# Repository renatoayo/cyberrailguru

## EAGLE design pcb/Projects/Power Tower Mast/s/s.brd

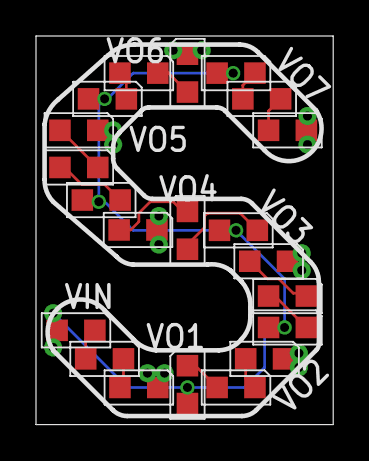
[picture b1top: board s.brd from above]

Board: 2 copper layers, 16.5 x 21.6 mm, 37 parts (0 on the bottom side), 22 nets.

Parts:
LED1, LED2, LED3, LED4, LED5, LED6, LED7, LED8, LED9, LED10, LED11, LED12, LED13, LED14, LED15, LED16, LED17, LED18, LED19, LED20, LED21: LED_0805
VIN, VIN1: P1-20
VO1, VO2, VO3, VO4, VO5, VO6, VO7, VO08, VO09, VO10, VO11, VO12, VO13, VO14: P1-20

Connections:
unnamed: LED19.C, LED20.A
unnamed: LED20.C, LED21.A
unnamed: LED2.C, LED3.A
unnamed: LED1.C, LED2.A
unnamed: LED5.C, LED6.A
unnamed: LED4.C, LED5.A
unnamed: LED8.C, LED9.A
unnamed: LED7.C, LED8.A
unnamed: LED11.C, LED12.A
unnamed: LED10.C, LED11.A
unnamed: LED14.C, LED15.A
unnamed: LED13.C, LED14.A
unnamed: LED17.C, LED18.A
unnamed: LED16.C, LED17.A
VIN: LED1.A, LED4.A, LED7.A, LED10.A, LED13.A, LED16.A, LED19.A, VIN.TP, VIN1.TP
VOUT1: LED3.C, VO1.TP, VO08.TP
VOUT2: LED6.C, VO2.TP, VO09.TP
VOUT3: LED9.C, VO3.TP, VO10.TP
VOUT4: LED12.C, VO4.TP, VO11.TP
VOUT5: LED15.C, VO5.TP, VO12.TP
VOUT6: LED18.C, VO6.TP, VO13.TP
VOUT7: LED21.C, VO7.TP, VO14.TP
